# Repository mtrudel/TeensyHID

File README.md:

# TeensyHID

A simple breakout board for the Teensy family of microcontrollers, providing:

* 7x3 Digital / Analog IO via JST connectors. Pin selection is optimized to allow for additional functions (I2C, DAC,
  etc) to be easily accessed.
* 2 M3 mounting holes

Pairs well with breakout boards such as my [Rotary Encoder breakout board](https://github.com/mtrudel/rotary_breakout).

Available at [OSH Park](https://oshpark.com/shared_projects/sCmXFWh1)

# License

MIT

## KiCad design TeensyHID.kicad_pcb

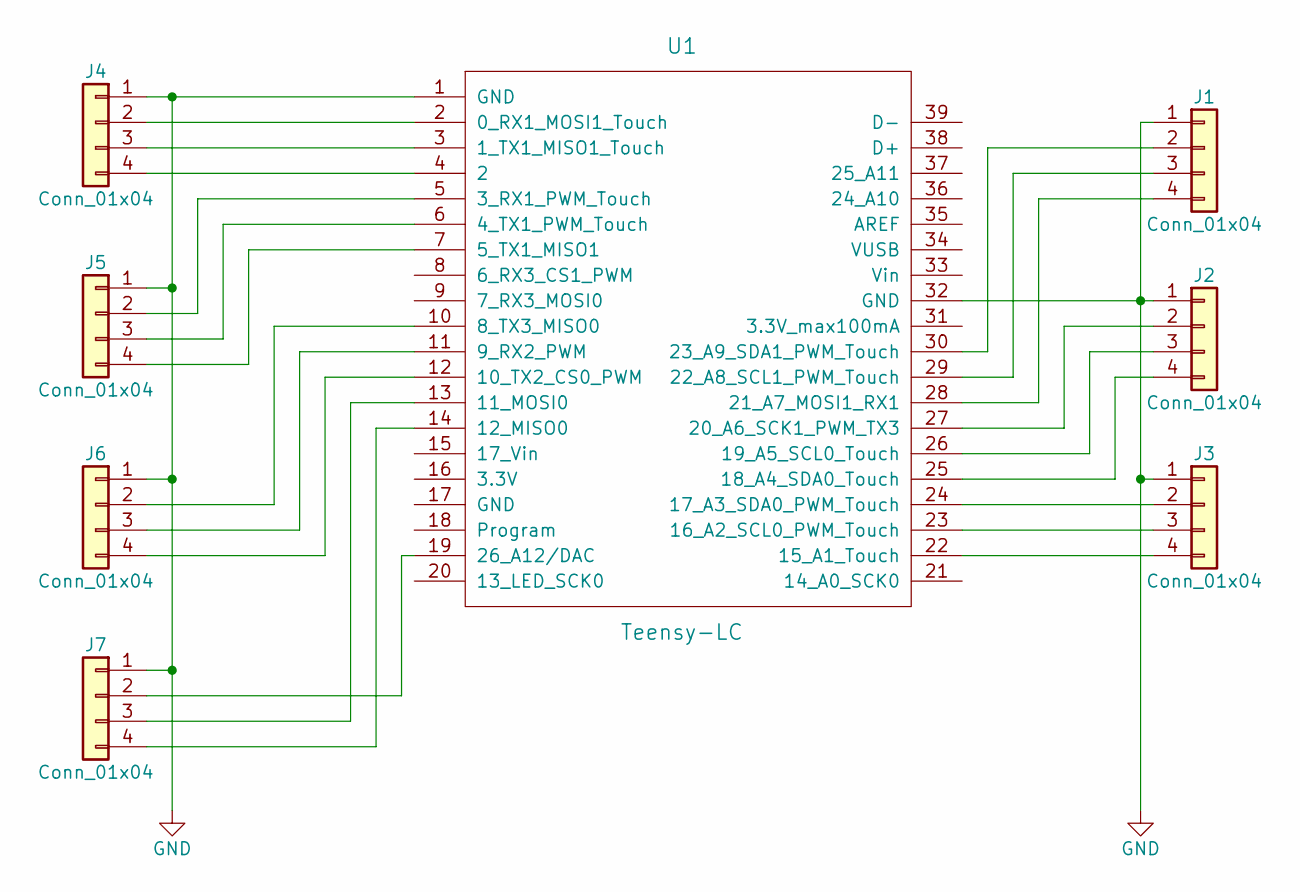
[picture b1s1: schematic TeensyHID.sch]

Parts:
J1, J2, J3, J4, J5, J6, J7: Conn_01x04; JST_EH_B04B-EH-A_04x2.50mm_Straight
U1: Teensy-LC; Teensy30_31_32_LC

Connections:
GND: J1.1, J2.1, J3.1, J4.1, J5.1, J6.1, J7.1, U1.1 (GND), U1.32 (GND)
unnamed: J1.2, U1.30 (23_A9_SDA1_PWM_Touch)
unnamed: J1.3, U1.29 (22_A8_SCL1_PWM_Touch)
unnamed: J1.4, U1.28 (21_A7_MOSI1_RX1)
unnamed: J2.2, U1.27 (20_A6_SCK1_PWM_TX3)
unnamed: J2.3, U1.26 (19_A5_SCL0_Touch)
unnamed: J2.4, U1.25 (18_A4_SDA0_Touch)
unnamed: J3.2, U1.24 (17_A3_SDA0_PWM_Touch)
unnamed: J3.3, U1.23 (16_A2_SCL0_PWM_Touch)
unnamed: J3.4, U1.22 (15_A1_Touch)
unnamed: J4.2, U1.2 (0_RX1_MOSI1_Touch)
unnamed: J4.3, U1.3 (1_TX1_MISO1_Touch)
unnamed: J4.4, U1.4 (2)
unnamed: J5.2, U1.5 (3_RX1_PWM_Touch)
unnamed: J5.3, U1.6 (4_TX1_PWM_Touch)
unnamed: J5.4, U1.7 (5_TX1_MISO1)
unnamed: J6.2, U1.10 (8_TX3_MISO0)
unnamed: J6.3, U1.11 (9_RX2_PWM)
unnamed: J6.4, U1.12 (10_TX2_CS0_PWM)
unnamed: J7.2, U1.19 (26_A12/DAC)
unnamed: J7.3, U1.13 (11_MOSI0)
unnamed: J7.4, U1.14 (12_MISO0)

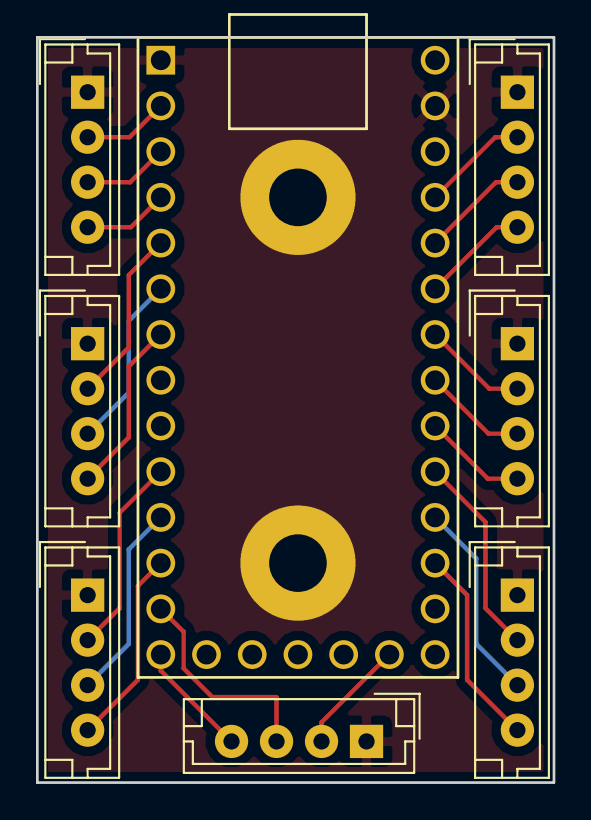
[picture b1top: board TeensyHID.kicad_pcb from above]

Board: 2 copper layers, 28.7 x 41.4 mm, 8 parts (0 on the bottom side), 22 nets.

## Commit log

2017-12-15 Initial 1.0 build of teensy HID
2018-01-19 1.1 build of TeensyHID
2018-01-22 2.0 build of TeensyHID
